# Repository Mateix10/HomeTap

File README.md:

# HomeTap
A haptic button that connects to HomeAssistant

I always wanted a premium button that is simple and only does a few actions - Toggle the lights on and off and change the color of the LEDs in my room.

# Design
For the design, I used a very simple and minimalistic look, while looking sleek and modern.

It features a LED ring made out of 24 RGB LEDs that light up when the user's finger gets close to the button. This design is inspired from the prototype steam box.

# Schematic and PCB
This device features a custom pcb. I used [kicad](https://www.kicad.org/).

# Credits
This project uses:

[KICAD](https://www.kicad.org/)

[Blender](https://www.blender.org/) - For renders

[HackClub Fallout](fallout.hackclub.com) - Founding

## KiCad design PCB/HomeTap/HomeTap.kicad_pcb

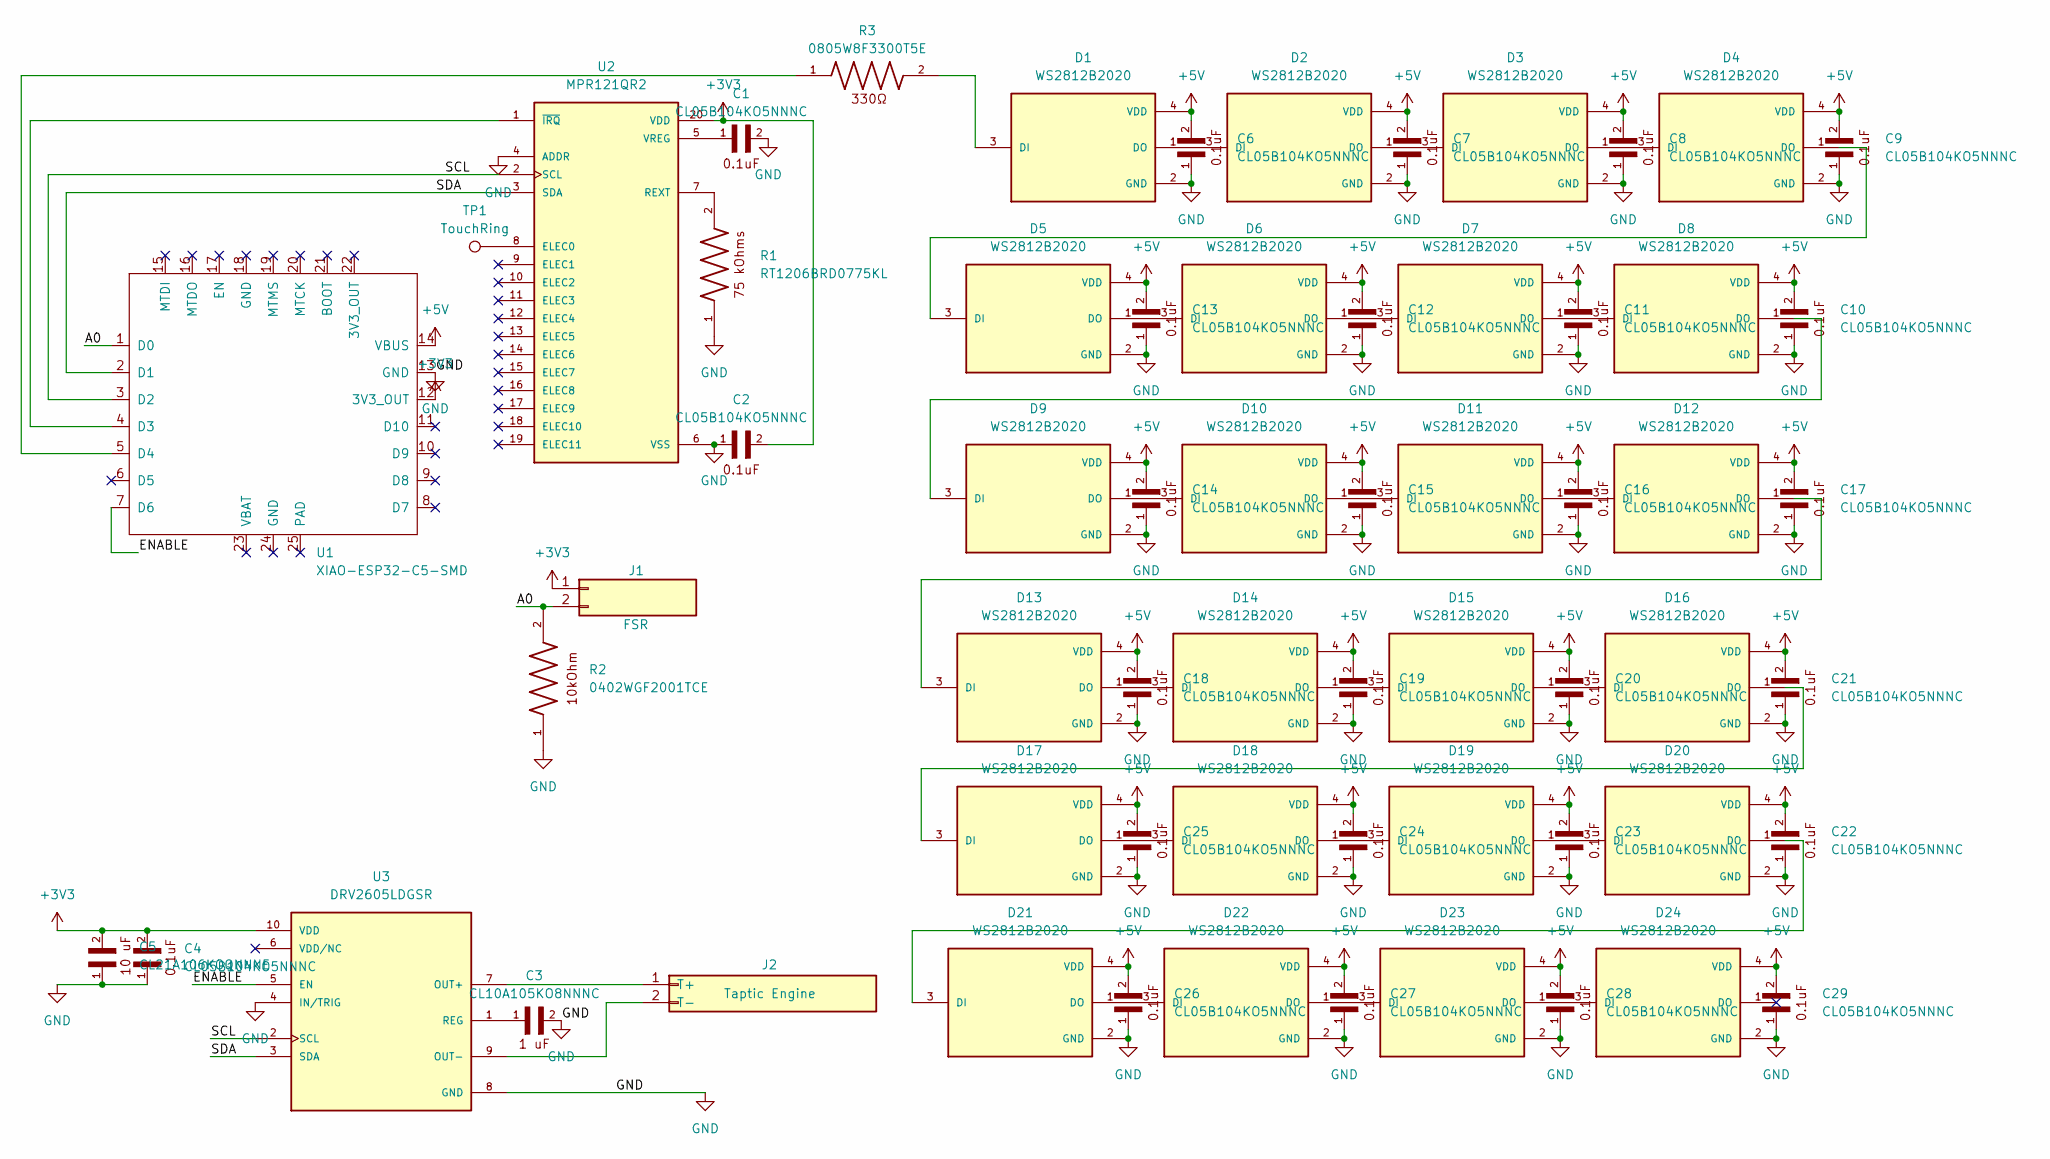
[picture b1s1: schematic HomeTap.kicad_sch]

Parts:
C1, C2, C4, C6, C7, C8, C9, C10, C11, C12, C13, C14, C15, C16, C17, C18, C19, C20, C21, C22, C23, C24, C25, C26, C27, C28, C29: CL05B104KO5NNNC; CAPC1005X55N; DigiKey_Part_Number 1276-1001-1-ND
C3: CL10A105KO8NNNC; CAPC1608X90N; DigiKey_Part_Number 1276-1034-1-ND
C5: CL21A106KOQNNNE; CAPC2012X140N
D1, D2, D3, D4, D5, D6, D7, D8, D9, D10, D11, D12, D13, D14, D15, D16, D17, D18, D19, D20, D21, D22, D23, D24: WS2812B2020; LED_WS2812B2020; PARTREV V1.0
J1: FSR
J2: Taptic Engine; SolderWire-0.5sqmm_1x02_P4.6mm_D0.9mm_OD2.1mm
R1: RT1206BRD0775KL; RESC3116X65N
R2: 0402WGF2001TCE; RESC1005X40N; PARTREV V3
R3: 0805W8F3300T5E; RESC2012X65N; PARTREV V3
TP1: TouchRing; TestPoint_Pad_D2.0mm
U1: XIAO-ESP32-C5-SMD; XIAO-ESP32-C5-DIP
U2: MPR121QR2; QFN40P300X300X60-20N
U3: DRV2605LDGSR; SOP50P490X110-10N; PARTREV D

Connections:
+3V3: C2.2, C4.2, C5.2, J1.1, U1.12 (3V3_OUT), U2.20 (VDD), U3.10 (VDD)
+5V: C6.2, C7.2, C8.2, C9.2, C10.2, C11.2, C12.2, C13.2, C14.2, C15.2, C16.2, C17.2, C18.2, C19.2, C20.2, C21.2, C22.2, C23.2, C24.2, C25.2, C26.2, C27.2, C28.2, C29.2, D1.4 (VDD), D2.4 (VDD), D3.4 (VDD), D4.4 (VDD), D5.4 (VDD), D6.4 (VDD), D7.4 (VDD), D8.4 (VDD), D9.4 (VDD), D10.4 (VDD), D11.4 (VDD), D12.4 (VDD), D13.4 (VDD), D14.4 (VDD), D15.4 (VDD), D16.4 (VDD), D17.4 (VDD), D18.4 (VDD), D19.4 (VDD), D20.4 (VDD), D21.4 (VDD), D22.4 (VDD), D23.4 (VDD), D24.4 (VDD), U1.14 (VBUS)
/A0: J1.2, R2.2, U1.1 (D0)
/ENABLE: U1.7 (D6), U3.5 (EN)
/SCL: U1.3 (D2), U2.2 (SCL), U3.2 (SCL)
/SDA: U1.2 (D1), U2.3 (SDA), U3.3 (SDA)
GND: C1.2, C2.1, C3.2, C4.1, C5.1, C6.1, C7.1, C8.1, C9.1, C10.1, C11.1, C12.1, C13.1, C14.1, C15.1, C16.1, C17.1, C18.1, C19.1, C20.1, C21.1, C22.1, C23.1, C24.1, C25.1, C26.1, C27.1, C28.1, C29.1, D1.2 (GND), D2.2 (GND), D3.2 (GND), D4.2 (GND), D5.2 (GND), D6.2 (GND), D7.2 (GND), D8.2 (GND), D9.2 (GND), D10.2 (GND), D11.2 (GND), D12.2 (GND), D13.2 (GND), D14.2 (GND), D15.2 (GND), D16.2 (GND), D17.2 (GND), D18.2 (GND), D19.2 (GND), D20.2 (GND), D21.2 (GND), D22.2 (GND), D23.2 (GND), D24.2 (GND), R1.1, R2.1, U1.13 (GND), U2.4 (ADDR), U2.6 (VSS), U3.4 (IN/TRIG), U3.8 (GND)
unnamed: D1.3 (DI), R3.2
unnamed: D1.1 (DO), D2.3 (DI)
unnamed: D2.1 (DO), D3.3 (DI)
unnamed: D3.1 (DO), D4.3 (DI)
unnamed: D4.1 (DO), D5.3 (DI)
unnamed: D5.1 (DO), D6.3 (DI)
unnamed: D6.1 (DO), D7.3 (DI)
unnamed: D7.1 (DO), D8.3 (DI)
unnamed: D8.1 (DO), D9.3 (DI)
unnamed: D9.1 (DO), D10.3 (DI)
unnamed: D10.1 (DO), D11.3 (DI)
unnamed: D11.1 (DO), D12.3 (DI)
unnamed: D12.1 (DO), D13.3 (DI)
unnamed: D13.1 (DO), D14.3 (DI)
unnamed: D14.1 (DO), D15.3 (DI)
unnamed: D15.1 (DO), D16.3 (DI)
unnamed: D16.1 (DO), D17.3 (DI)
unnamed: D17.1 (DO), D18.3 (DI)
unnamed: D18.1 (DO), D19.3 (DI)
unnamed: D19.1 (DO), D20.3 (DI)
unnamed: D20.1 (DO), D21.3 (DI)
unnamed: D21.1 (DO), D22.3 (DI)
unnamed: D22.1 (DO), D23.3 (DI)
unnamed: D23.1 (DO), D24.3 (DI)
unnamed: J2.1 (T+), U3.7 (OUT+)
unnamed: J2.2 (T-), U3.9 (OUT-)
unnamed: U1.4 (D3), U2.1 (~IRQ)
unnamed: R3.1, U1.5 (D4)
unnamed: TP1.1, U2.8 (ELEC0)
unnamed: R1.2, U2.7 (REXT)
unnamed: C1.1, U2.5 (VREG)
unnamed: C3.1, U3.1 (REG)

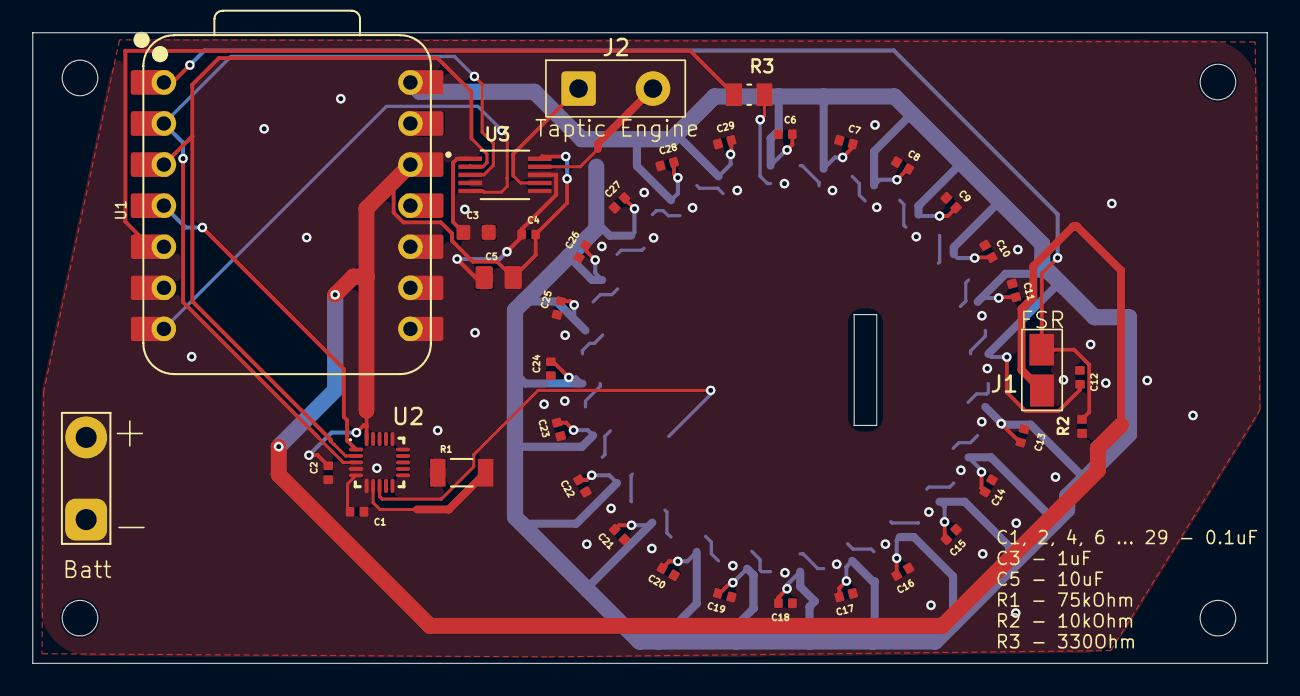
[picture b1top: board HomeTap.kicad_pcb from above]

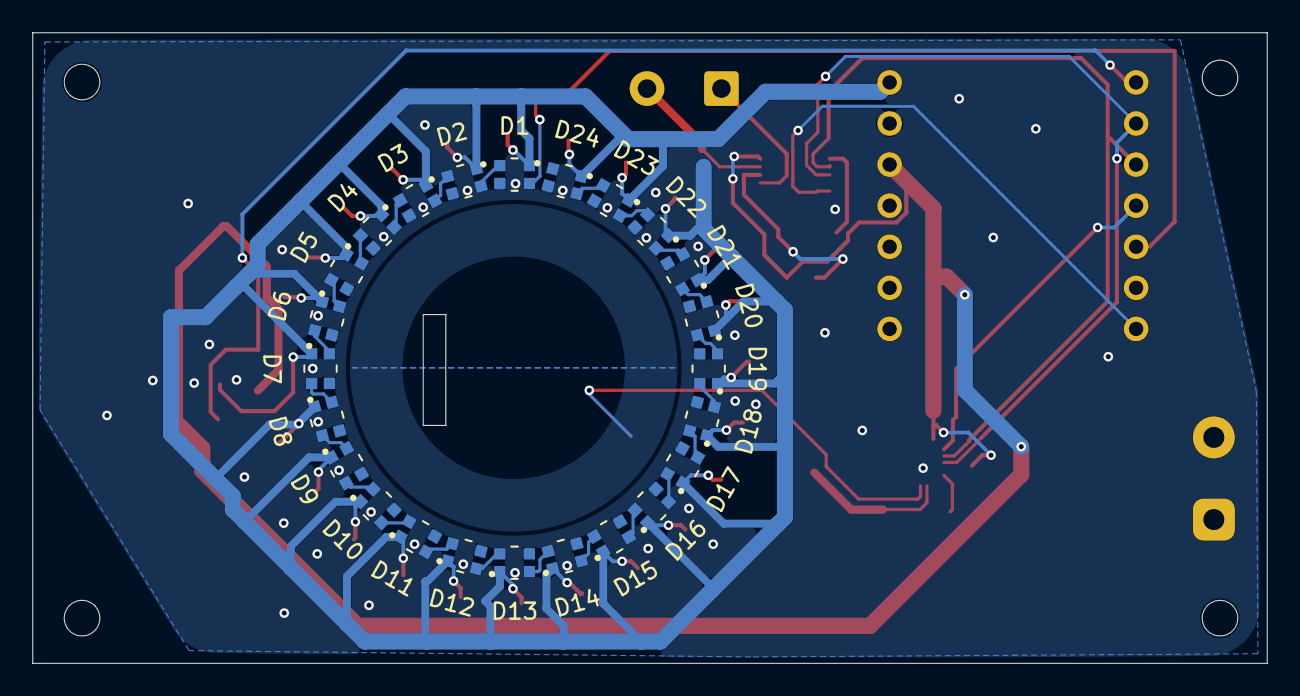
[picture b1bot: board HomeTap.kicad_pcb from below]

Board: 2 copper layers, 76.3 x 39.0 mm, 62 parts (24 on the bottom side), 38 nets.
